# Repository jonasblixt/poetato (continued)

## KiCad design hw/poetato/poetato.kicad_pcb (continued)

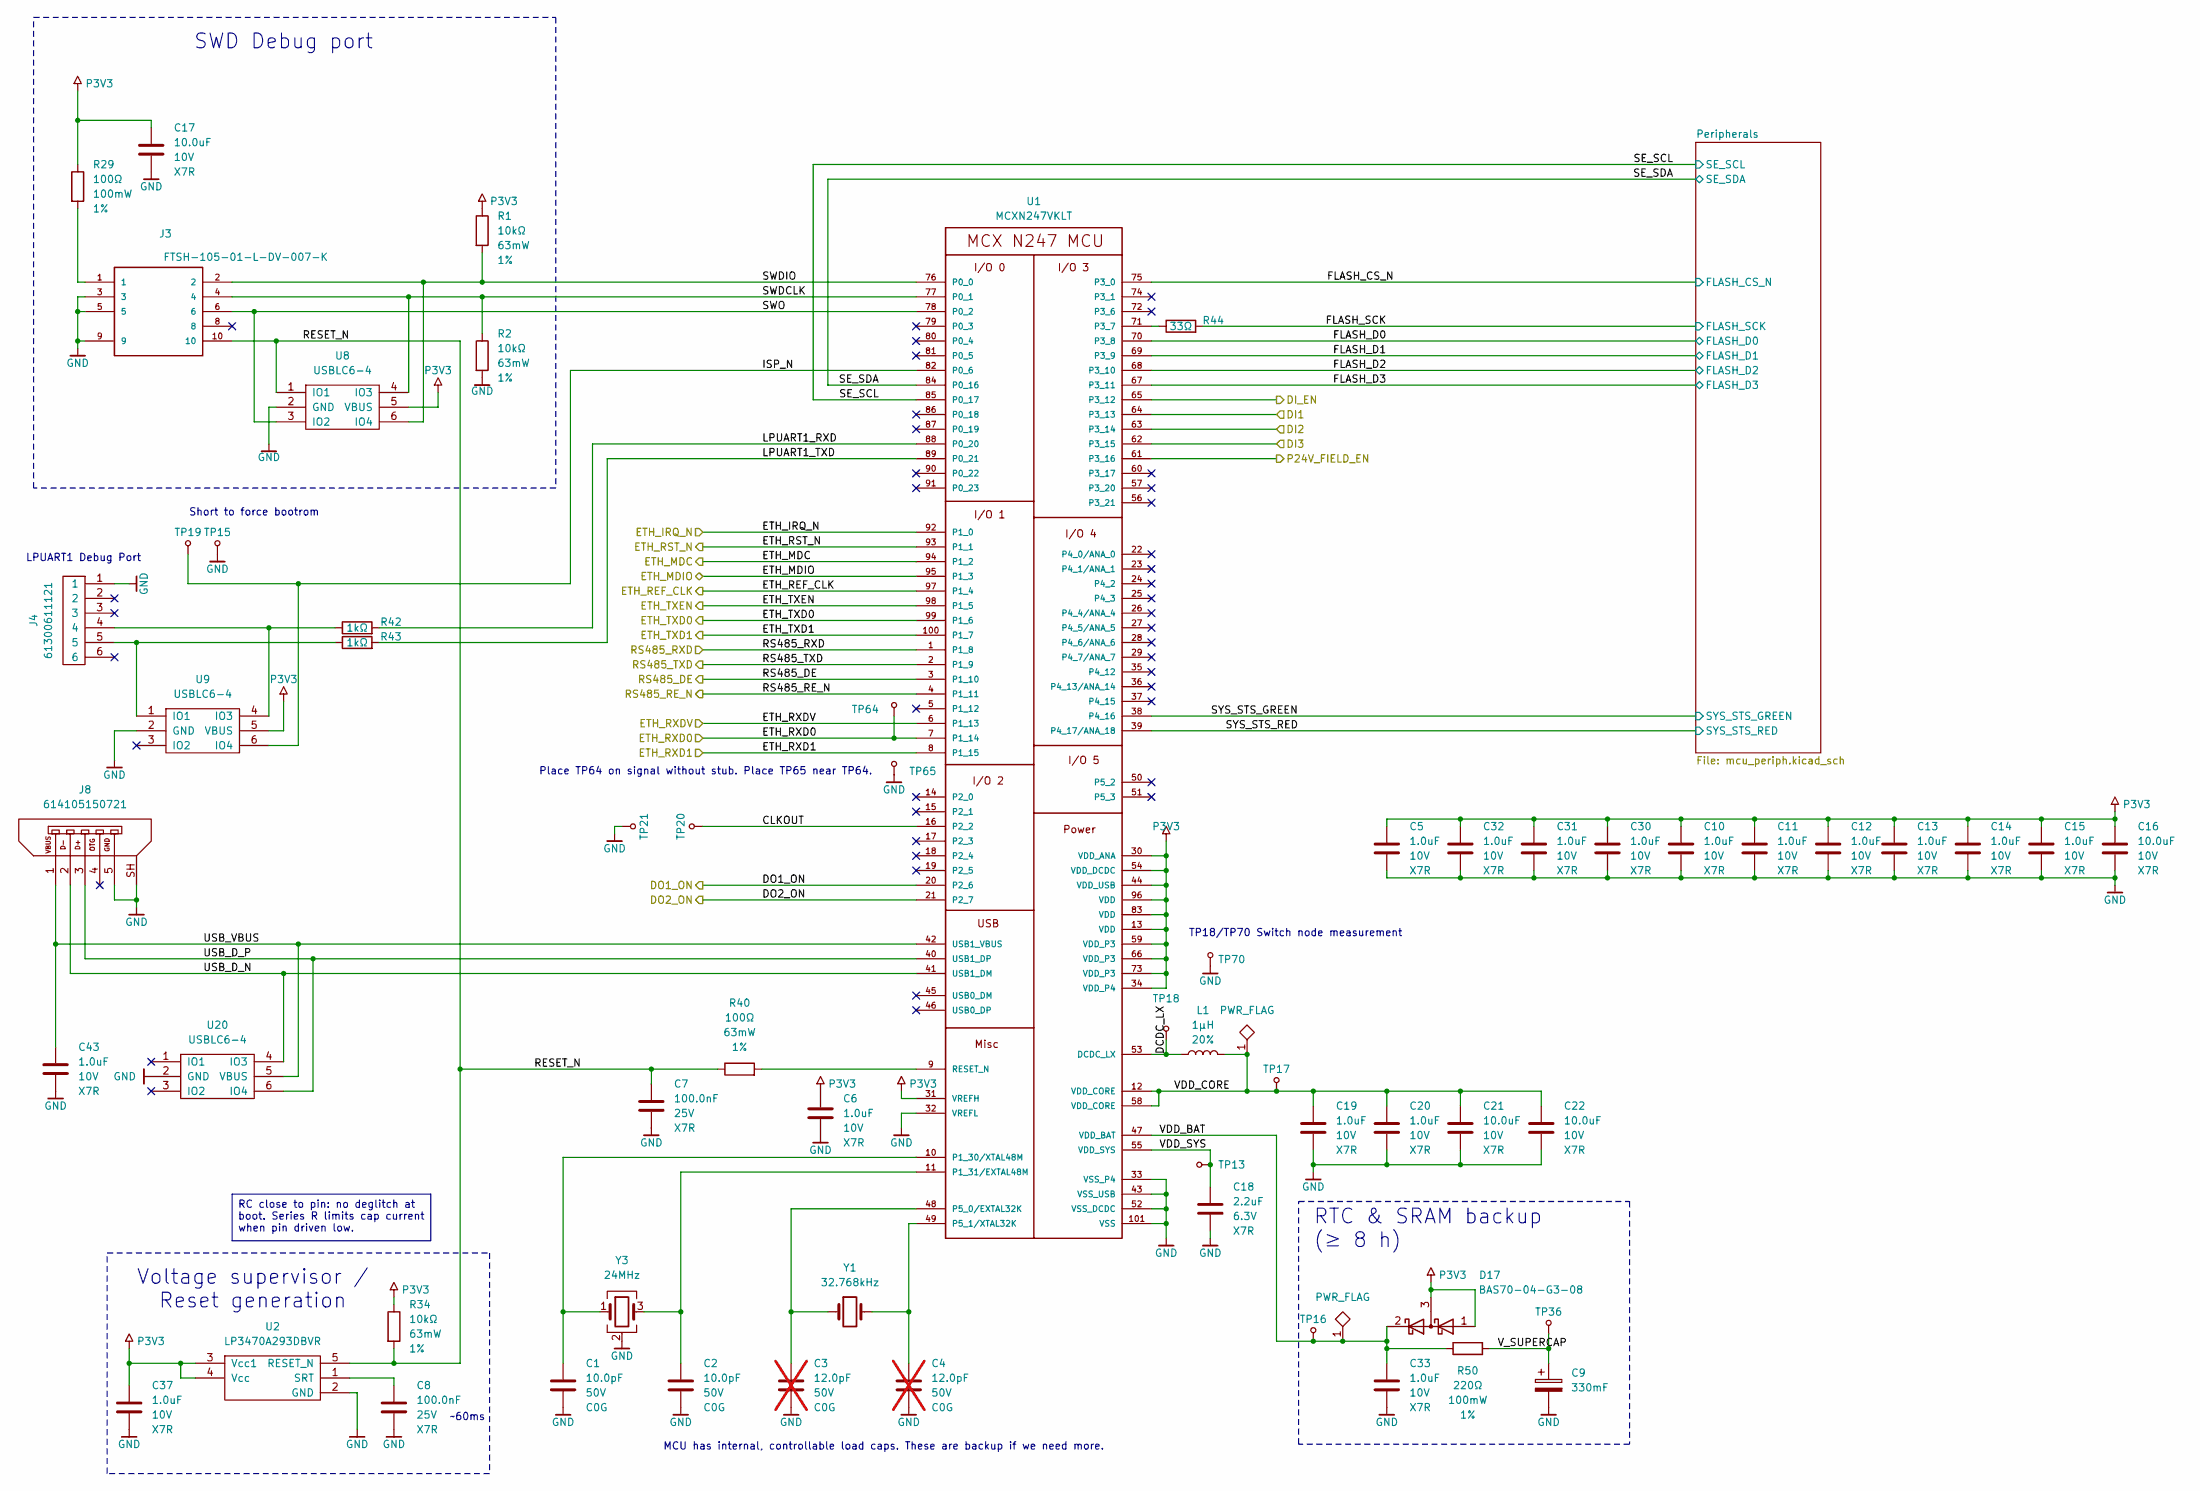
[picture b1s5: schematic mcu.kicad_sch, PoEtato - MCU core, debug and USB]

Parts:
C1, C2: 10.0pF; C_0402_1005Metric; Voltage 50V; Part Number GRM1555C1H100GA01
C3, C4: 12.0pF; C_0402_1005Metric; Voltage 50V; Part Number GRM1555C1H120GA01; not fitted
C5, C6, C10, C11, C12, C13, C14, C15, C19, C20, C30, C31, C32, C33, C37, C43: 1.0uF; C_0402_1005Metric; Voltage 10V; Part Number GRM155Z71A105KE01
C7, C8: 100.0nF; C_0402_1005Metric; Voltage 25V; Part Number GRM155R71E104KE14
C9: 330mF; Eaton_KW_13.5x8.8mm; Voltage 5.5V; Part Number KW-5R5C334H-R
C16, C17, C21, C22: 10.0uF; C_0805_2012Metric; Voltage 10V; Part Number GRM21BR71A106KA73
C18: 2.2uF; C_0603_1608Metric; Voltage 6.3V; Part Number GRM188R70J225KE15
D17: BAS70-04-G3-08; SOT-23; Part Number BAS70-04-G3-08
J3: FTSH-105-01-L-DV-007-K; SAMTEC_FTSH-105-01-L-DV-007-K; Part Number FTSH-105-01-L-DV-007-K-TR
J4: 61300611121; PinHeader_1x06_P2.54mm_Vertical; Part Number 61300611121
J8: 614105150721; USB_Micro-B_Wuerth_614105150721_Vertical; Part Number 614105150721
L1: 1µH; IHLP1212AE; Tolerance 20%; Part Number IHLP1212AEEZ1R0M1Z
R1, R2, R34: 10kΩ; R_0402_1005Metric; Tolerance 1%; Part Number CRCW040210K0FKED
R29: 100Ω; R_0603_1608Metric; Tolerance 1%; Part Number CRCW0603100RFKEA
R40: 100Ω; R_0402_1005Metric; Tolerance 1%; Part Number CRCW0402100RFKED
R42, R43: 1kΩ; R_0402_1005Metric; Tolerance 1%; Part Number CRCW04021K00FKED
R44: 33Ω; R_0402_1005Metric; Tolerance 1%; Part Number CRCW040233R0FKED
R50: 220Ω; R_0603_1608Metric; Tolerance 1%; Part Number CRCW0603220RFKEA
TP13, TP15, TP16, TP17, TP18, TP19, TP20, TP21, TP36, TP64, TP65, TP70: TP; TestPoint_Pad_D1.0mm
U1: MCXN247VKLT; LQFP-100-1EP_14x14mm_P0.5mm_EP6.9x6.9mm; Part Number MCXN247VKLT
U2: LP3470A293DBVR; SOT-23-5; Part Number LP3470A293DBVR
U8, U9, U20: USBLC6-4; SOT-23-6; Part Number USBLC6-4SC6Y
Y1: 32.768kHz; NX3215SA; Frequency Tolerance ±20ppm; Part Number X1A0001410006
Y3: 24MHz; NX3225SA; Frequency Tolerance ±10ppm; Part Number X1E0000210048

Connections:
/Ethernet & PoE/ETH_IRQ_N: U1.92 (P1_0); also elsewhere on the board
/Ethernet & PoE/ETH_MDC: U1.94 (P1_2); also elsewhere on the board
/Ethernet & PoE/ETH_MDIO: U1.95 (P1_3); also elsewhere on the board
/Ethernet & PoE/ETH_REF_CLK: U1.97 (P1_4); also elsewhere on the board
/Ethernet & PoE/ETH_RST_N: U1.93 (P1_1); also elsewhere on the board
/Ethernet & PoE/ETH_RXD0: TP64.1, U1.7 (P1_14); also elsewhere on the board
/Ethernet & PoE/ETH_RXD1: U1.8 (P1_15); also elsewhere on the board
/Ethernet & PoE/ETH_RXDV: U1.6 (P1_13); also elsewhere on the board
/Ethernet & PoE/ETH_TXD0: U1.99 (P1_6); also elsewhere on the board
/Ethernet & PoE/ETH_TXD1: U1.100 (P1_7); also elsewhere on the board
/Ethernet & PoE/ETH_TXEN: U1.98 (P1_5); also elsewhere on the board
/IO/DI1: U1.64 (P3_13); also elsewhere on the board
/IO/DI2: U1.63 (P3_14); also elsewhere on the board
/IO/DI3: U1.62 (P3_15); also elsewhere on the board
/IO/DI_EN: U1.65 (P3_12); also elsewhere on the board
/MCU/CLKOUT: TP20.1, U1.16 (P2_2)
/MCU/DCDC_LX: L1.1, TP18.1, U1.53 (DCDC_LX)
/MCU/DO1_ON: U1.20 (P2_6); also elsewhere on the board
/MCU/DO2_ON: U1.21 (P2_7); also elsewhere on the board
/MCU/FLASH_CS_N: U1.75 (P3_0); also elsewhere on the board
/MCU/FLASH_D0: U1.70 (P3_8); also elsewhere on the board
/MCU/FLASH_D1: U1.69 (P3_9); also elsewhere on the board
/MCU/FLASH_D2: U1.68 (P3_10); also elsewhere on the board
/MCU/FLASH_D3: U1.67 (P3_11); also elsewhere on the board
/MCU/FLASH_SCK: R44.2; also elsewhere on the board
/MCU/ISP_N: TP19.1, U1.82 (P0_6), U9.6 (IO4)
/MCU/LPUART1_RXD: R42.2, U1.88 (P0_20)
/MCU/LPUART1_TXD: R43.2, U1.89 (P0_21)
/MCU/P24V_FIELD_EN: U1.61 (P3_16); also elsewhere on the board
/MCU/RESET_N: C7.1, J3.10, R34.2, R40.1, U2.5 (RESET_N), U8.1 (IO1)
/MCU/RS485_DE: U1.3 (P1_10); also elsewhere on the board
/MCU/RS485_RE_N: U1.4 (P1_11); also elsewhere on the board
/MCU/RS485_RXD: U1.1 (P1_8); also elsewhere on the board
/MCU/RS485_TXD: U1.2 (P1_9); also elsewhere on the board
/MCU/SE_SCL: U1.85 (P0_17); also elsewhere on the board
/MCU/SE_SDA: U1.84 (P0_16); also elsewhere on the board
/MCU/SWDCLK: J3.4, R2.1, U1.77 (P0_1), U8.4 (IO3)
/MCU/SWDIO: J3.2, R1.2, U1.76 (P0_0), U8.6 (IO4)
/MCU/SWO: J3.6, U1.78 (P0_2), U8.3 (IO2)
/MCU/SYS_STS_GREEN: U1.38 (P4_16); also elsewhere on the board
/MCU/SYS_STS_RED: U1.39 (P4_17/ANA_18); also elsewhere on the board
/MCU/USB_D_N: J8.2, U1.41 (USB1_DM), U20.4 (IO3)
/MCU/USB_D_P: J8.3, U1.40 (USB1_DP), U20.6 (IO4)
/MCU/USB_VBUS: C43.1, J8.1, U1.42 (USB1_VBUS), U20.5 (VBUS)
/MCU/VDD_BAT: C33.1, D17.2 (K), R50.1, TP16.1, U1.47 (VDD_BAT)
/MCU/VDD_CORE: C19.1, C20.1, C21.1, C22.1, L1.2, TP17.1, U1.12 (VDD_CORE), U1.58 (VDD_CORE)
/MCU/VDD_SYS: C18.1, TP13.1, U1.55 (VDD_SYS)
/MCU/V_SUPERCAP: C9.1, R50.2, TP36.1
GND: C1.2, C2.2, C3.2, C4.2, C5.2, C6.2, C7.2, C8.2, C9.2, C10.2, C11.2, C12.2, C13.2, C14.2, C15.2, C16.2, C17.2, C18.2, C19.2, C20.2, C21.2, C22.2, C30.2, C31.2, C32.2, C33.2, C37.2, C43.2, J3.3, J3.5, J3.9, J4.1, J8.5, J8.SH, R2.2, TP15.1, TP21.1, TP65.1, TP70.1, U1.32 (VREFL), U1.33 (VSS_P4), U1.43 (VSS_USB), U1.52 (VSS_DCDC), U1.101 (VSS), U2.2 (GND), U8.2 (GND), U9.2 (GND), U20.2 (GND), Y3.2 (G), Y3.4 (G); also elsewhere on the board
unnamed: J3.1, R29.2
unnamed: C1.1, U1.10 (P1_30/XTAL48M), Y3.1
unnamed: C2.1, U1.11 (P1_31/EXTAL48M), Y3.3
unnamed: R44.1, U1.71 (P3_7)
unnamed: C3.1, U1.48 (P5_0/EXTAL32K), Y1.1
unnamed: C4.1, U1.49 (P5_1/XTAL32K), Y1.2
unnamed: R40.2, U1.9 (RESET_N)
unnamed: C8.1, U2.1 (SRT)
unnamed: J4.5, R43.1, U9.1 (IO1)
unnamed: J4.4, R42.1, U9.4 (IO3)
P3V3: C5.1, C6.1, C10.1, C11.1, C12.1, C13.1, C14.1, C15.1, C16.1, C17.1, C30.1, C31.1, C32.1, C37.1, D17.1 (A), D17.3 (common), R1.1, R29.1, R34.1, U1.13 (VDD), U1.30 (VDD_ANA), U1.31 (VREFH), U1.34 (VDD_P4), U1.44 (VDD_USB), U1.54 (VDD_DCDC), U1.59 (VDD_P3), U1.66 (VDD_P3), U1.73 (VDD_P3), U1.83 (VDD), U1.96 (VDD), U2.3 (Vcc1), U2.4 (Vcc), U8.5 (VBUS), U9.5 (VBUS); also elsewhere on the board

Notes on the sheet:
~60ms
RTC & SRAM backup (≥ 8 h)
Voltage supervisor / Reset generation
SWD Debug port
MCU has internal, controllable load caps. These are backup if we need more.
Short to force bootrom
LPUART1 Debug Port
Place TP64 on signal without stub. Place TP65 near TP64.
TP18/TP70 Switch node measurement
RC close to pin: no deglitch at boot. Series R limits cap current when pin driven low.

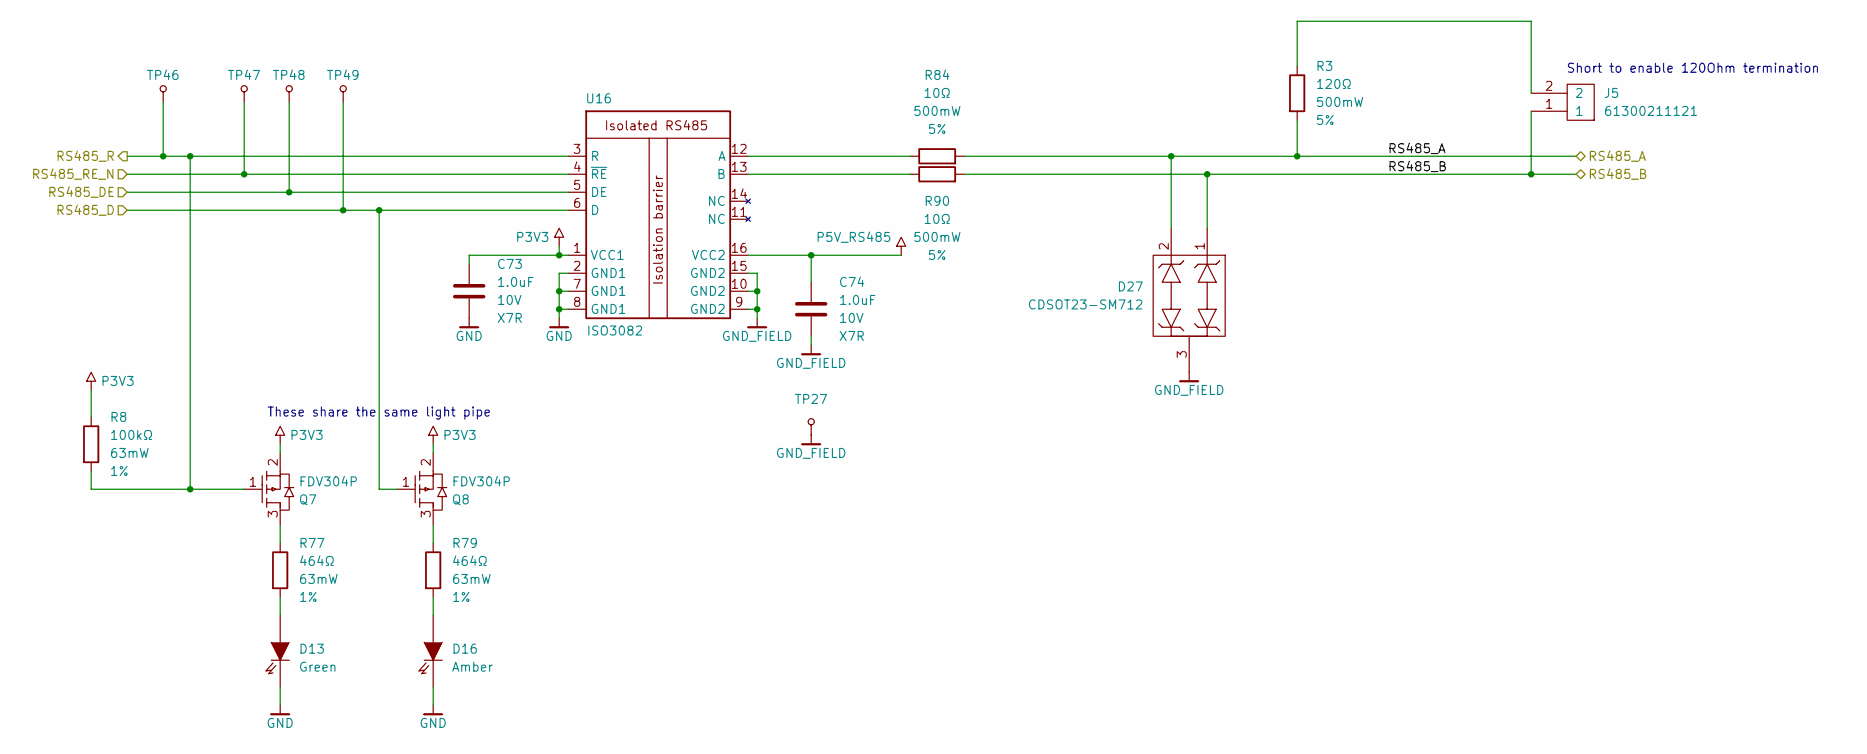
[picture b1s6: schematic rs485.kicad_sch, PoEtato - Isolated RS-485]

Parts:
C73, C74: 1.0uF; C_0402_1005Metric; Voltage 10V; Part Number GRM155Z71A105KE01
D13: LED0402_150040VS73240; LED_0402_1005Metric; Part Number 150040VS73240
D16: LED0402_150040AS73240; LED_0402_1005Metric; Part Number 150040AS73240
D27: CDSOT23-SM712; SOT-23; Part Number CDSOT23-SM712
J5: 61300211121; PinHeader_1x02_P2.54mm_Vertical; Part Number 61300211121
Q7, Q8: FDV304P; SOT-23; Part Number FDV304P
R3: 120Ω; R_1210_3225Metric; Tolerance 5%; Part Number ERJT14J121U
R8: 100kΩ; R_0402_1005Metric; Tolerance 1%; Part Number CRCW0402100KFKED
R77, R79: 464Ω; R_0402_1005Metric; Tolerance 1%; Part Number CRCW0402464RFKED
R84, R90: 10Ω; R_1210_3225Metric; Tolerance 5%; Part Number ERJT14J100U
TP27, TP46, TP47, TP48, TP49: TP; TestPoint_Pad_D1.0mm
U16: ISO3082; SOIC-16W_7.5x10.3mm_P1.27mm; Part Number ISO3082DWR

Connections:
/IO/RS485/RS485_A: D27.2, R3.2, R84.2; also elsewhere on the board
/IO/RS485/RS485_B: D27.1, J5.1, R90.2; also elsewhere on the board
/MCU/RS485_DE: TP48.1, U16.5 (DE); also elsewhere on the board
/MCU/RS485_RE_N: TP47.1, U16.4 (~RE); also elsewhere on the board
/MCU/RS485_RXD: Q7.1, R8.2, TP46.1, U16.3 (R); also elsewhere on the board
/MCU/RS485_TXD: Q8.1, TP49.1, U16.6 (D); also elsewhere on the board
GND: C73.2, D13.1, D16.1, U16.2 (GND1), U16.7 (GND1), U16.8 (GND1); also elsewhere on the board
GND_FIELD: C74.2, D27.3, TP27.1, U16.9 (GND2), U16.10 (GND2), U16.15 (GND2); also elsewhere on the board
unnamed: D13.2, R77.2
unnamed: D16.2, R79.2
unnamed: J5.2, R3.1
unnamed: Q7.3, R77.1
unnamed: Q8.3, R79.1
unnamed: R84.1, U16.12 (A)
unnamed: R90.1, U16.13 (B)
P3V3: C73.1, Q7.2, Q8.2, R8.1, U16.1 (VCC1); also elsewhere on the board
P5V_RS485: C74.1, U16.16 (VCC2); also elsewhere on the board

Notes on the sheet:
These share the same light pipe
Short to enable 120Ohm termination

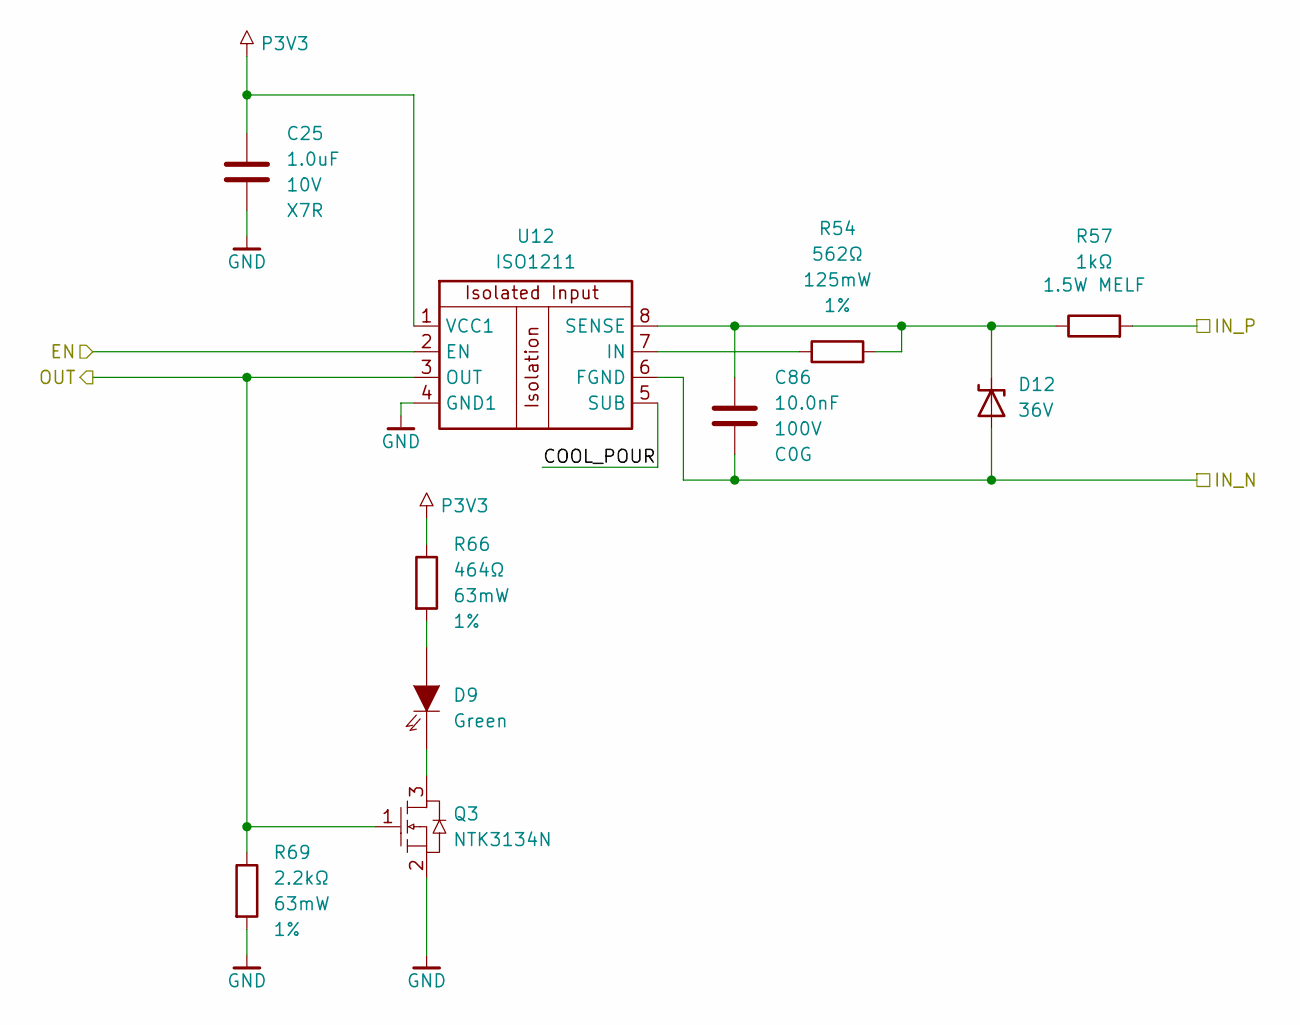
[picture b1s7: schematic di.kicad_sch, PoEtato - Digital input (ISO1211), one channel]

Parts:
C25: 1.0uF; C_0402_1005Metric; Voltage 10V; Part Number GRM155Z71A105KE01
C86: 10.0nF; C_0805_2012Metric; Voltage 100V; Part Number GRM2195C2A103JA01
D9: LED0402_150040VS73240; LED_0402_1005Metric; Part Number 150040VS73240
D12: 36V; D_SOD-123; Part Number SMF36A
Q3: NTK3134N; SOT-723; Part Number NTK3134NT1G
R54: 562Ω; R_0805_2012Metric; Tolerance 1%; Part Number CRCW0805562RFKEA
R57: 1kΩ; R_MiniMELF_MMA-0204; Part Number SMM02040C1001FB300
R66: 464Ω; R_0402_1005Metric; Tolerance 1%; Part Number CRCW0402464RFKED
R69: 2.2kΩ; R_0402_1005Metric; Tolerance 1%; Part Number CRCW04022K20FKED
U12: ISO1211; SOIC-8_3.9x4.9mm_P1.27mm; Part Number ISO1211DR

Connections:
/IO/DI1: Q3.1, R69.1, U12.3 (OUT); also elsewhere on the board
/IO/DI1/COOL_POUR: U12.5 (SUB)
/IO/DI_EN: U12.2 (EN); also elsewhere on the board
/IO/IN1_N: C86.2, D12.2 (A2), U12.6 (FGND); also elsewhere on the board
/IO/IN1_P: R57.2; also elsewhere on the board
GND: C25.2, Q3.2, R69.2, U12.4 (GND1); also elsewhere on the board
unnamed: D9.1, Q3.3
unnamed: D9.2, R66.2
unnamed: C86.1, D12.1 (A1), R54.2, R57.1, U12.8 (SENSE)
unnamed: R54.1, U12.7 (IN)
P3V3: C25.1, R66.1, U12.1 (VCC1); also elsewhere on the board

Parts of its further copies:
C26, C27: 1.0uF; C_0402_1005Metric; Voltage 10V; Part Number GRM155Z71A105KE01
C87, C88: 10.0nF; C_0805_2012Metric; Voltage 100V; Part Number GRM2195C2A103JA01
D10, D11: LED0402_150040VS73240; LED_0402_1005Metric; Part Number 150040VS73240
D20, D21: 36V; D_SOD-123; Part Number SMF36A
Q11, Q13: NTK3134N; SOT-723; Part Number NTK3134NT1G
R55, R56: 562Ω; R_0805_2012Metric; Tolerance 1%; Part Number CRCW0805562RFKEA
R58, R59: 1kΩ; R_MiniMELF_MMA-0204; Part Number SMM02040C1001FB300
R67, R68: 464Ω; R_0402_1005Metric; Tolerance 1%; Part Number CRCW0402464RFKED
R70, R71: 2.2kΩ; R_0402_1005Metric; Tolerance 1%; Part Number CRCW04022K20FKED
U13, U14: ISO1211; SOIC-8_3.9x4.9mm_P1.27mm; Part Number ISO1211DR

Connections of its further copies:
/IO/DI2: Q11.1, R70.1, U13.3 (OUT); also elsewhere on the board
/IO/DI2/COOL_POUR: U13.5 (SUB)
/IO/DI3: Q13.1, R71.1, U14.3 (OUT); also elsewhere on the board
/IO/DI3/COOL_POUR: U14.5 (SUB)
/IO/DI_EN: U13.2 (EN), U14.2 (EN); also elsewhere on the board
/IO/IN2_N: C87.2, D20.2 (A2), U13.6 (FGND); also elsewhere on the board
/IO/IN2_P: R58.2; also elsewhere on the board
/IO/IN3_N: C88.2, D21.2 (A2), U14.6 (FGND); also elsewhere on the board
/IO/IN3_P: R59.2; also elsewhere on the board
GND: C26.2, C27.2, Q11.2, Q13.2, R70.2, R71.2, U13.4 (GND1), U14.4 (GND1); also elsewhere on the board
unnamed: D10.1, Q11.3
unnamed: D10.2, R67.2
unnamed: D11.1, Q13.3
unnamed: D11.2, R68.2
unnamed: C87.1, D20.1 (A1), R55.2, R58.1, U13.8 (SENSE)
unnamed: C88.1, D21.1 (A1), R56.2, R59.1, U14.8 (SENSE)
unnamed: R55.1, U13.7 (IN)
unnamed: R56.1, U14.7 (IN)
P3V3: C26.1, C27.1, R67.1, R68.1, U13.1 (VCC1), U14.1 (VCC1); also elsewhere on the board

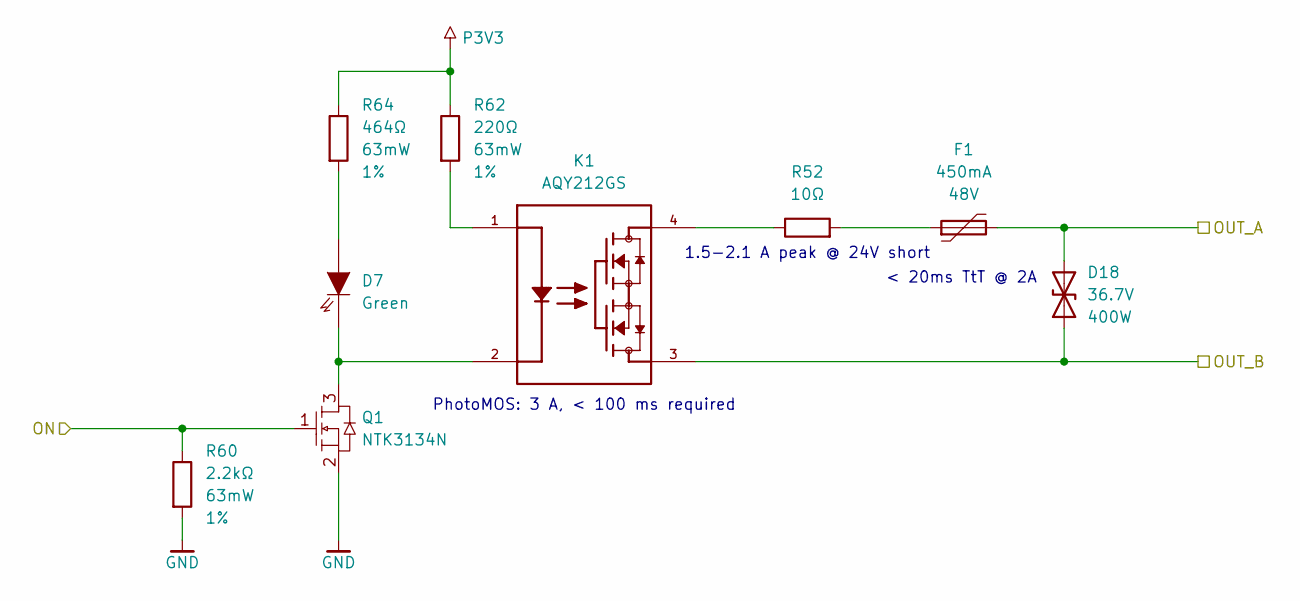
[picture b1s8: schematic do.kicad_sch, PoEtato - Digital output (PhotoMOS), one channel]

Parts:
D7: LED0402_150040VS73240; LED_0402_1005Metric; Part Number 150040VS73240
D18: 36.7V; D_SMA; Breakdown Voltage 36.7V; Standoff Voltage 33V; Part Number SMAJ33CA
F1: 450mA; FUSC3216X85N; Max Voltage 48V; Part Number 0ZCJ0016FF2E
K1: AQY212GS; SOIC254P680X230-4N; Part Number AQY212GS
Q1: NTK3134N; SOT-723; Part Number NTK3134NT1G
R52: 10Ω; R_2512_6332Metric; Part Number CRCW251210R0FKEGHP
R60: 2.2kΩ; R_0402_1005Metric; Tolerance 1%; Part Number CRCW04022K20FKED
R62: 220Ω; R_0402_1005Metric; Tolerance 1%; Part Number CRCW0402220RFKED
R64: 464Ω; R_0402_1005Metric; Tolerance 1%; Part Number CRCW0402464RFKED

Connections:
/IO/OUT1_A: D18.2 (A2), F1.2; also elsewhere on the board
/IO/OUT1_B: D18.1 (A1), K1.3; also elsewhere on the board
/MCU/DO1_ON: Q1.1, R60.1; also elsewhere on the board
GND: Q1.2, R60.2; also elsewhere on the board
unnamed: D7.1, K1.2, Q1.3
unnamed: D7.2, R64.2
unnamed: F1.1, R52.2
unnamed: K1.1, R62.2
unnamed: K1.4, R52.1
P3V3: R62.1, R64.1; also elsewhere on the board

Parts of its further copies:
D8: LED0402_150040VS73240; LED_0402_1005Metric; Part Number 150040VS73240
D19: 36.7V; D_SMA; Breakdown Voltage 36.7V; Standoff Voltage 33V; Part Number SMAJ33CA
F2: 450mA; FUSC3216X85N; Max Voltage 48V; Part Number 0ZCJ0016FF2E
K2: AQY212GS; SOIC254P680X230-4N; Part Number AQY212GS
Q12: NTK3134N; SOT-723; Part Number NTK3134NT1G
R53: 10Ω; R_2512_6332Metric; Part Number CRCW251210R0FKEGHP
R61: 2.2kΩ; R_0402_1005Metric; Tolerance 1%; Part Number CRCW04022K20FKED
R65: 464Ω; R_0402_1005Metric; Tolerance 1%; Part Number CRCW0402464RFKED
R96: 220Ω; R_0402_1005Metric; Tolerance 1%; Part Number CRCW0402220RFKED

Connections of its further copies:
/IO/OUT2_A: D19.2 (A2), F2.2; also elsewhere on the board
/IO/OUT2_B: D19.1 (A1), K2.3; also elsewhere on the board
/MCU/DO2_ON: Q12.1, R61.1; also elsewhere on the board
GND: Q12.2, R61.2; also elsewhere on the board
unnamed: D8.1, K2.2, Q12.3
unnamed: D8.2, R65.2
unnamed: F2.1, R53.2
unnamed: K2.1, R96.2
unnamed: K2.4, R53.1
P3V3: R65.1, R96.1; also elsewhere on the board

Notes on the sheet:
< 20ms TtT @ 2A
PhotoMOS: 3 A, < 100 ms required
1.5-2.1 A peak @ 24V short

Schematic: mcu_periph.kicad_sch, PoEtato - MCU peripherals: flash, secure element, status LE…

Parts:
C23, C24: 1.0uF; C_0402_1005Metric; Voltage 10V; Part Number GRM155Z71A105KE01
D14: LED0402_150040VS73240; LED_0402_1005Metric; Part Number 150040VS73240
D15: LED0402_150040SS73240; LED_0402_1005Metric; Part Number 150040SS73240
Q9, Q10: NTK3134N; SOT-723; Part Number NTK3134NT1G
R45, R46, R47: 10kΩ; R_0402_1005Metric; Tolerance 1%; Part Number CRCW040210K0FKED
R48, R49, R91, R93: 2.2kΩ; R_0402_1005Metric; Tolerance 1%; Part Number CRCW04022K20FKED
R92, R94: 464Ω; R_0402_1005Metric; Tolerance 1%; Part Number CRCW0402464RFKED
TP37, TP38, TP39, TP55, TP56, TP57, TP58, TP59, TP60, TP61: TP; TestPoint_Pad_D1.0mm
U10: SE051; UQFN-20-1EP_3x3mm_P0.4mm_EP1.85x1.85mm; Part Number SE051C2HQ1/Z01XDZ
U11: S25FL064LABMFI013; SOIC-8_5.3x5.3mm_P1.27mm; Part Number S25FL064LABMFI013

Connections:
/MCU/FLASH_CS_N: R45.2, TP60.1, U11.1 (#CS); also elsewhere on the board
/MCU/FLASH_D0: TP56.1, U11.5 (SI/SIO0); also elsewhere on the board
/MCU/FLASH_D1: TP57.1, U11.2 (SP/SIO1); also elsewhere on the board
/MCU/FLASH_D2: R46.2, TP58.1, U11.3 (#WP/SIO2); also elsewhere on the board
/MCU/FLASH_D3: R47.2, TP59.1, U11.7 (#RESET/SIO3); also elsewhere on the board
/MCU/FLASH_SCK: TP61.1, U11.6 (SCLK); also elsewhere on the board
/MCU/SE_SCL: R49.2, TP39.1, U10.10 (I2C_SCL); also elsewhere on the board
/MCU/SE_SDA: R48.2, TP38.1, U10.9 (I2C_SDA); also elsewhere on the board
/MCU/SYS_STS_GREEN: Q9.1, R91.1; also elsewhere on the board
/MCU/SYS_STS_RED: Q10.1, R93.1; also elsewhere on the board
GND: C23.2, C24.2, Q9.2, Q10.2, R91.2, R93.2, TP37.1, TP55.1, U10.1 (ISO_14443_LB), U10.14 (ISO_7816_RST_N), U10.17 (ISO_14443_LA), U10.19 (Vss), U10.21 (Vss), U11.4 (GND); also elsewhere on the board
unnamed: D14.1, Q9.3
unnamed: D14.2, R92.2
unnamed: D15.1, Q10.3
unnamed: D15.2, R94.2
P3V3: C23.1, C24.1, R45.1, R46.1, R47.1, R48.1, R49.1, R92.1, R94.1, U10.11 (ENA), U10.12 (VIN), U10.18 (Vcc), U11.8 (Vcc); also elsewhere on the board

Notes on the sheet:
Secure Element
System status LEDs
D14 and D15 share the same light pipe
8MiB Mass storage flash

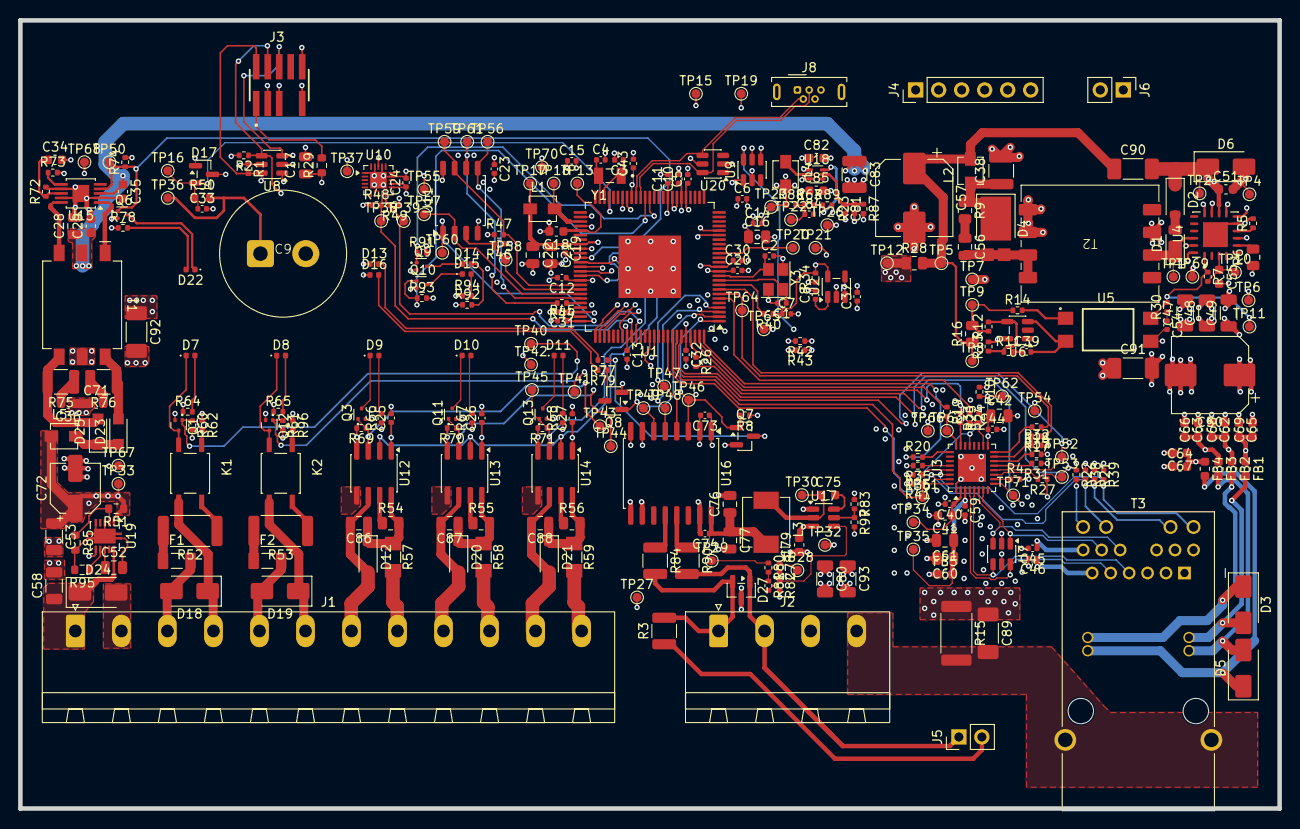
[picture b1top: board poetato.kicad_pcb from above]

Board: 6 copper layers, 139.0 x 87.0 mm, 336 parts (0 on the bottom side), 186 nets.
